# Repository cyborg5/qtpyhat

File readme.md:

# QT Py Hat Software

This is the software bundle that goes with an upcoming Adafruit Learning Guide.

It is an infrared remote control that is controlled via a webpage over your local Wi-Fi network.

Uses a Raspberry Pi Zero W, an Adafruit QT Py SAMD21, and a custom open-source board to connect them and add infrared receiver and transmitter circuitry.

When complete, the learning guide will be available at
https://learn.adafruit.com/iot-ir-remote-using-raspberry-pi-zero-w-and-qtpy-hat/

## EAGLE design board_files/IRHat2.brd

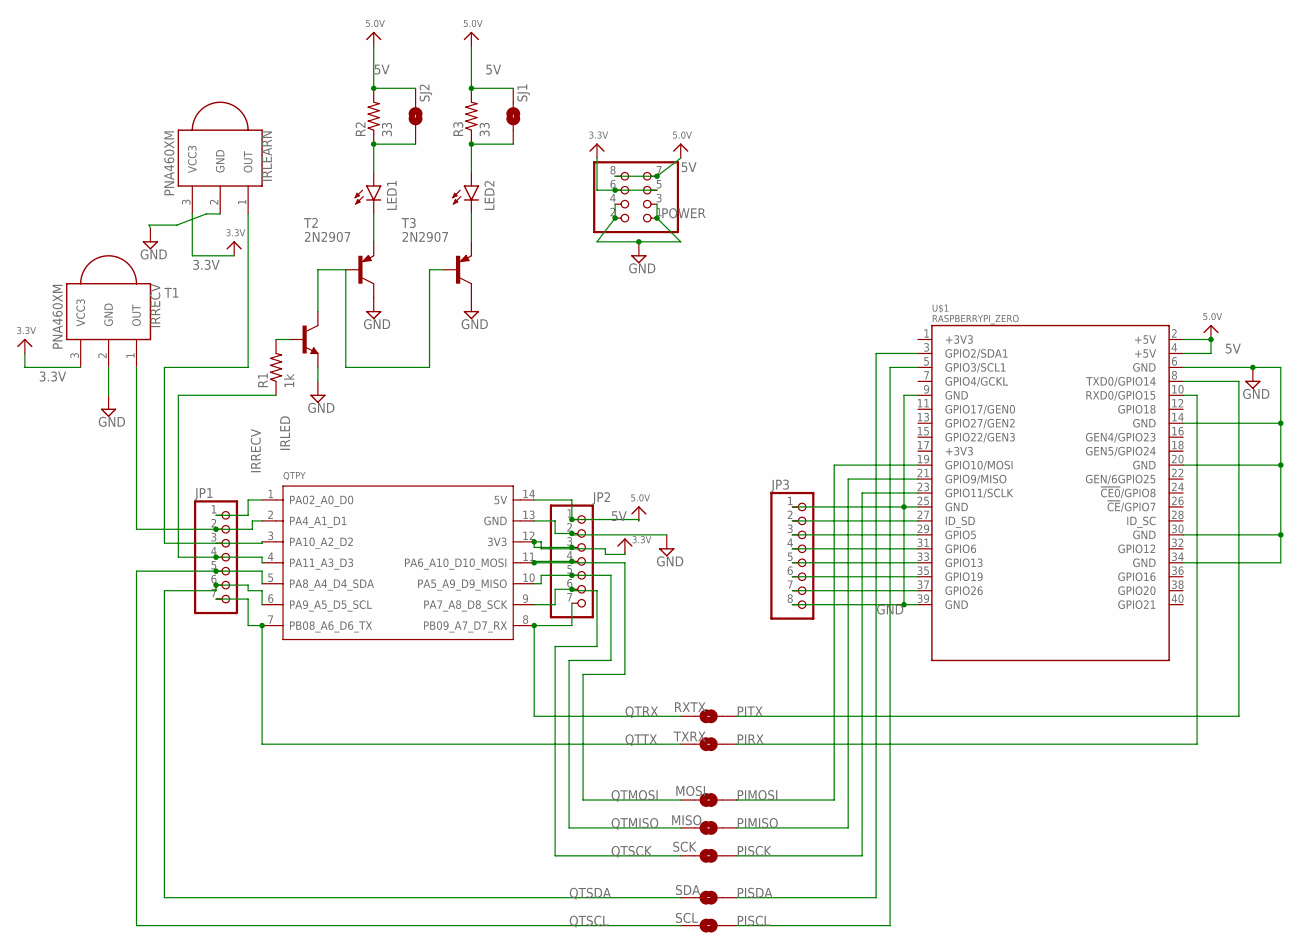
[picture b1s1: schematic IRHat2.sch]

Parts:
IRLEARN: PNA460XM
IRRECV: PNA460XM
JP1, JP2: PINHD-1X7; 1X07
JP3: PINHD-1X8CLEANBIG; 1X08-CLEANBIG
LED1, LED2: LED-IRTSAL6100; LED_5MM
MISO: SPARKFUN_SOLDERJUMPERNO; SPARKFUN_SJ_2S-NO
MOSI: SPARKFUN_SOLDERJUMPERNO; SPARKFUN_SJ_2S-NO
POWER: PINHD-2X4; 2X04
QTPY: MOUDLE-SEEEDUINO-XIAO; MOUDLE14P-2.54-21X17.8MM
R1: 1k; 0204/5
R2, R3: 33; 0204/5
RXTX: SPARKFUN_SOLDERJUMPERTRACE; SPARKFUN_SJ_2S-TRACE
SCK: SPARKFUN_SOLDERJUMPERNO; SPARKFUN_SJ_2S-NO
SCL: SPARKFUN_SOLDERJUMPERNO; SPARKFUN_SJ_2S-NO
SDA: SPARKFUN_SOLDERJUMPERNO; SPARKFUN_SJ_2S-NO
SJ1, SJ2: SPARKFUN_SOLDERJUMPERTRACE; SPARKFUN_SJ_2S-TRACE
T1: -NPN-TO92-EBC; TO92-EBC
T2, T3: 2N2907; TO92-CBE
TXRX: SPARKFUN_SOLDERJUMPERTRACE; SPARKFUN_SJ_2S-TRACE
U$1: RASPBERRYPI_ZERO

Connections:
3.3V: IRLEARN.3 (VCC3), IRRECV.3 (VCC3), JP2.3, POWER.5, POWER.6, QTPY.12 (3V3)
5V: JP2.1, POWER.7, POWER.8, QTPY.14 (5V), R2.2, R3.2, SJ1.2, SJ2.2, U$1.2 (+5V), U$1.4 (+5V)
GND: IRLEARN.2 (GND), IRRECV.2 (GND), JP2.2, JP3.1, JP3.8, POWER.1, POWER.2, POWER.3, POWER.4, QTPY.13 (GND), T1.E, T2.C, T3.C, U$1.6 (GND), U$1.9 (GND), U$1.14 (GND), U$1.20 (GND), U$1.25 (GND), U$1.30 (GND), U$1.34 (GND), U$1.39 (GND)
IRLED: JP1.4, QTPY.4 (PA11_A3_D3), R1.1
IRRECV: IRRECV.1 (OUT), JP1.2, QTPY.2 (PA4_A1_D1)
unnamed: JP3.2, U$1.27 (ID_SD)
unnamed: JP3.3, U$1.29 (GPIO5)
unnamed: LED1.K (C), T2.E
unnamed: R1.2, T1.B
unnamed: LED2.K (C), T3.E
unnamed: JP3.4, U$1.31 (GPIO6)
unnamed: LED2.A, R3.1, SJ1.1
unnamed: T1.C, T2.B, T3.B
unnamed: JP1.1, QTPY.1 (PA02_A0_D0)
unnamed: LED1.A, R2.1, SJ2.1
unnamed: JP3.5, U$1.33 (GPIO13)
unnamed: IRLEARN.1 (OUT), JP1.3, QTPY.3 (PA10_A2_D2)
unnamed: JP3.6, U$1.35 (GPIO19)
unnamed: JP3.7, U$1.37 (GPIO26)
PIMISO: MISO.2, U$1.21 (GPIO9/MISO)
PIMOSI: MOSI.2, U$1.19 (GPIO10/MOSI)
PIRX: TXRX.2, U$1.10 (RXD0/GPIO15)
PISCK: SCK.2, U$1.23 (GPIO11/SCLK)
PISCL: SCL.2, U$1.5 (GPIO3/SCL1)
PISDA: SDA.2, U$1.3 (GPIO2/SDA1)
PITX: RXTX.2, U$1.8 (TXD0/GPIO14)
QTMISO: JP2.5, MISO.1, QTPY.10 (PA5_A9_D9_MISO)
QTMOSI: JP2.4, MOSI.1, QTPY.11 (PA6_A10_D10_MOSI)
QTRX: JP2.7, QTPY.8 (PB09_A7_D7_RX), RXTX.1
QTSCK: JP2.6, QTPY.9 (PA7_A8_D8_SCK), SCK.1
QTSCL: JP1.5, QTPY.5 (PA8_A4_D4_SDA), SCL.1
QTSDA: JP1.6, QTPY.6 (PA9_A5_D5_SCL), SDA.1
QTTX: JP1.7, QTPY.7 (PB08_A6_D6_TX), TXRX.1

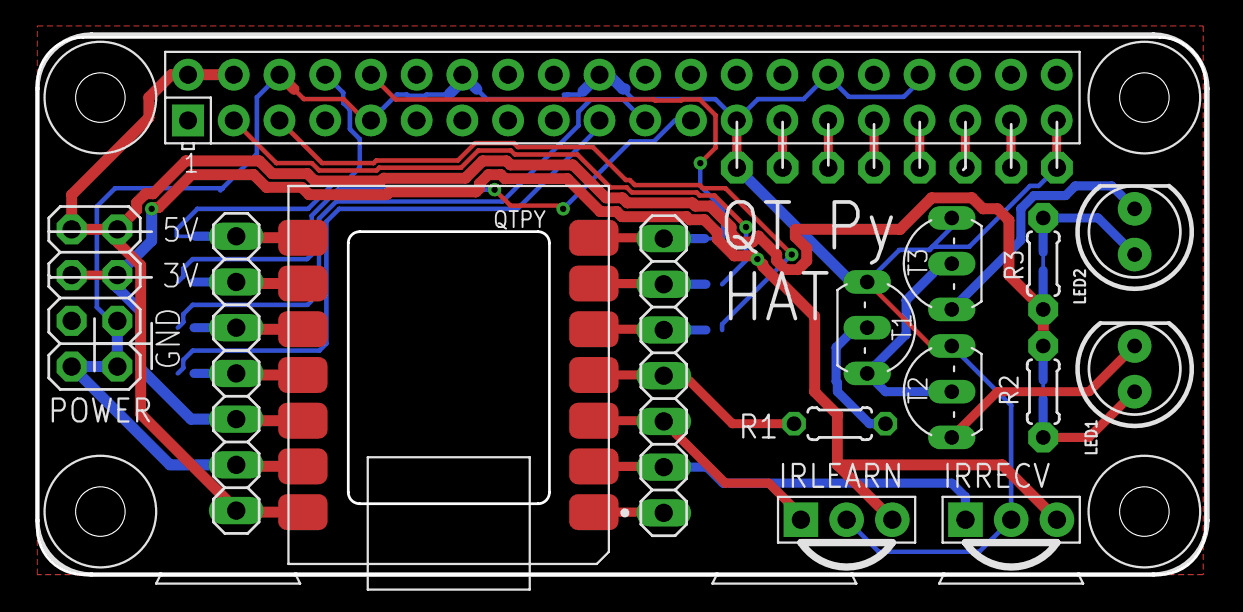
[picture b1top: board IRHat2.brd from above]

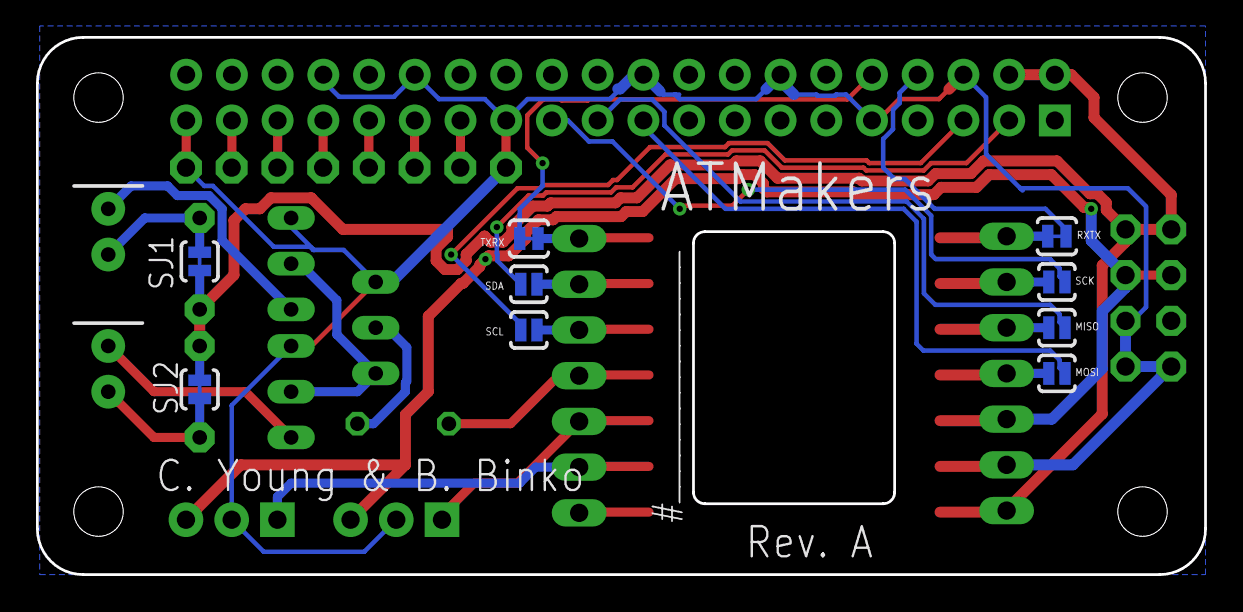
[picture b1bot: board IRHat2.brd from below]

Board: 2 copper layers, 64.9 x 29.8 mm, 25 parts (9 on the bottom side), 33 nets.

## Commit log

2021-04-10 Added echo program
    Added echo program
2021-04-11 Further updates
    Further updates
2021-04-15 Added CAD files
    Added CAD files

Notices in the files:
parts and their libraries:
SparkFun-LED: Licensing: Creative Commons ShareAlike 4.0 International - https://creativecommons.org/licenses/by-sa/4.0
microbuilder: This work is placed in the public domain, and may be freely used for commercial and non-commercial work with the following conditions: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
